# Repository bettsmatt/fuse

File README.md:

# Fuse
A WIP split, 60%, wireless, low profile, choc spaced, magnetic keyboard. 

## Design Notes

* 3D printed case with embedded magnets to allow the two split boards to snap together into a single board. 
* Switches must be soldered as the footprint of hotswap sockets would space the switches too far apart.
* Through hole diode matrix as they look badass and SMD parts are a pain to solder. 
* Wireless (no TRRS), Nice!Nano with 3.7v batteries. Power Switch on PCB.
* PCBs are reversible for the left / right hand. Nice!Nano pins mirrored in ZMK firmware.

## PCB

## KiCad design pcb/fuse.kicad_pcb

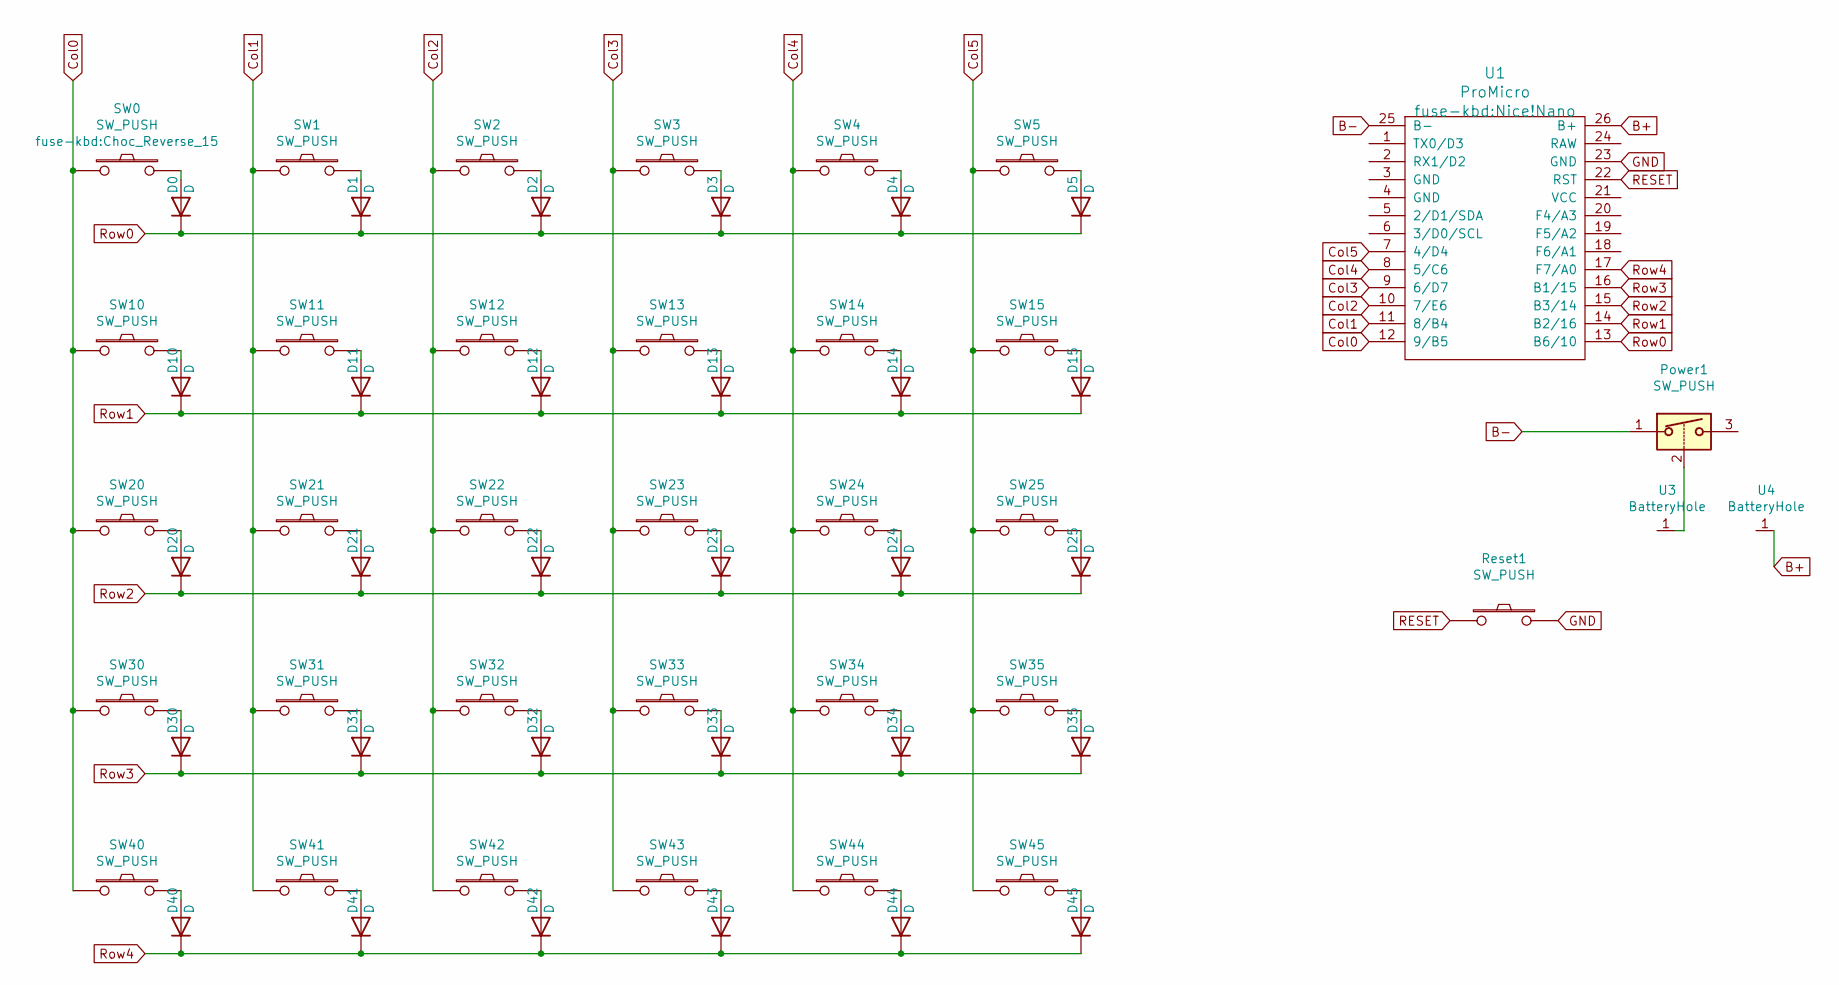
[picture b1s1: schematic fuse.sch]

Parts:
D0, D1, D2, D3, D4, D5, D10, D11, D12, D13, D14, D15, D20, D21, D22, D23, D24, D25, D30, D31, D32, D33, D34, D35, D40, D41, D42, D43, D44, D45: D; R
Power1: SW_PUSH; EG1218
Reset1: SW_PUSH; Reset
SW0, SW10, SW20, SW30, SW45: SW_PUSH; Choc_Reverse_15
SW1, SW2, SW3, SW4, SW5, SW11, SW12, SW13, SW14, SW15, SW21, SW22, SW23, SW24, SW25, SW31, SW32, SW33, SW34, SW35, SW40, SW41, SW42, SW43, SW44: SW_PUSH; Choc_Reverse
U1: ProMicro; Nice!Nano
U3, U4: BatteryHole; BatteryPins

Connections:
B+: U1.26 (B+), U4.1
B-: Power1.1, U1.25 (B-)
Col0: SW0.1, SW10.1, SW20.1, SW30.1, SW40.1, U1.12 (9/B5)
Col1: SW1.1, SW11.1, SW21.1, SW31.1, SW41.1, U1.11 (8/B4)
Col2: SW2.1, SW12.1, SW22.1, SW32.1, SW42.1, U1.10 (7/E6)
Col3: SW3.1, SW13.1, SW23.1, SW33.1, SW43.1, U1.9 (6/D7)
Col4: SW4.1, SW14.1, SW24.1, SW34.1, SW44.1, U1.8 (5/C6)
Col5: SW5.1, SW15.1, SW25.1, SW35.1, SW45.1, U1.7 (4/D4)
GND: Reset1.2, U1.23 (GND)
unnamed: D0.2 (A), SW0.2
unnamed: D1.2 (A), SW1.2
unnamed: D2.2 (A), SW2.2
unnamed: D3.2 (A), SW3.2
unnamed: D4.2 (A), SW4.2
unnamed: D5.2 (A), SW5.2
unnamed: D10.2 (A), SW10.2
unnamed: D11.2 (A), SW11.2
unnamed: D12.2 (A), SW12.2
unnamed: D13.2 (A), SW13.2
unnamed: D14.2 (A), SW14.2
unnamed: D15.2 (A), SW15.2
unnamed: D20.2 (A), SW20.2
unnamed: D21.2 (A), SW21.2
unnamed: D22.2 (A), SW22.2
unnamed: D23.2 (A), SW23.2
unnamed: D24.2 (A), SW24.2
unnamed: D25.2 (A), SW25.2
unnamed: D30.2 (A), SW30.2
unnamed: D31.2 (A), SW31.2
unnamed: D32.2 (A), SW32.2
unnamed: D33.2 (A), SW33.2
unnamed: D34.2 (A), SW34.2
unnamed: D35.2 (A), SW35.2
unnamed: D40.2 (A), SW40.2
unnamed: D41.2 (A), SW41.2
unnamed: D42.2 (A), SW42.2
unnamed: D43.2 (A), SW43.2
unnamed: D44.2 (A), SW44.2
unnamed: D45.2 (A), SW45.2
unnamed: Power1.2, U3.1
RESET: Reset1.1, U1.22 (RST)
Row0: D0.1 (K), D1.1 (K), D2.1 (K), D3.1 (K), D4.1 (K), D5.1 (K), U1.13 (B6/10)
Row1: D10.1 (K), D11.1 (K), D12.1 (K), D13.1 (K), D14.1 (K), D15.1 (K), U1.14 (B2/16)
Row2: D20.1 (K), D21.1 (K), D22.1 (K), D23.1 (K), D24.1 (K), D25.1 (K), U1.15 (B3/14)
Row3: D30.1 (K), D31.1 (K), D32.1 (K), D33.1 (K), D34.1 (K), D35.1 (K), U1.16 (B1/15)
Row4: D40.1 (K), D41.1 (K), D42.1 (K), D43.1 (K), D44.1 (K), D45.1 (K), U1.17 (F7/A0)

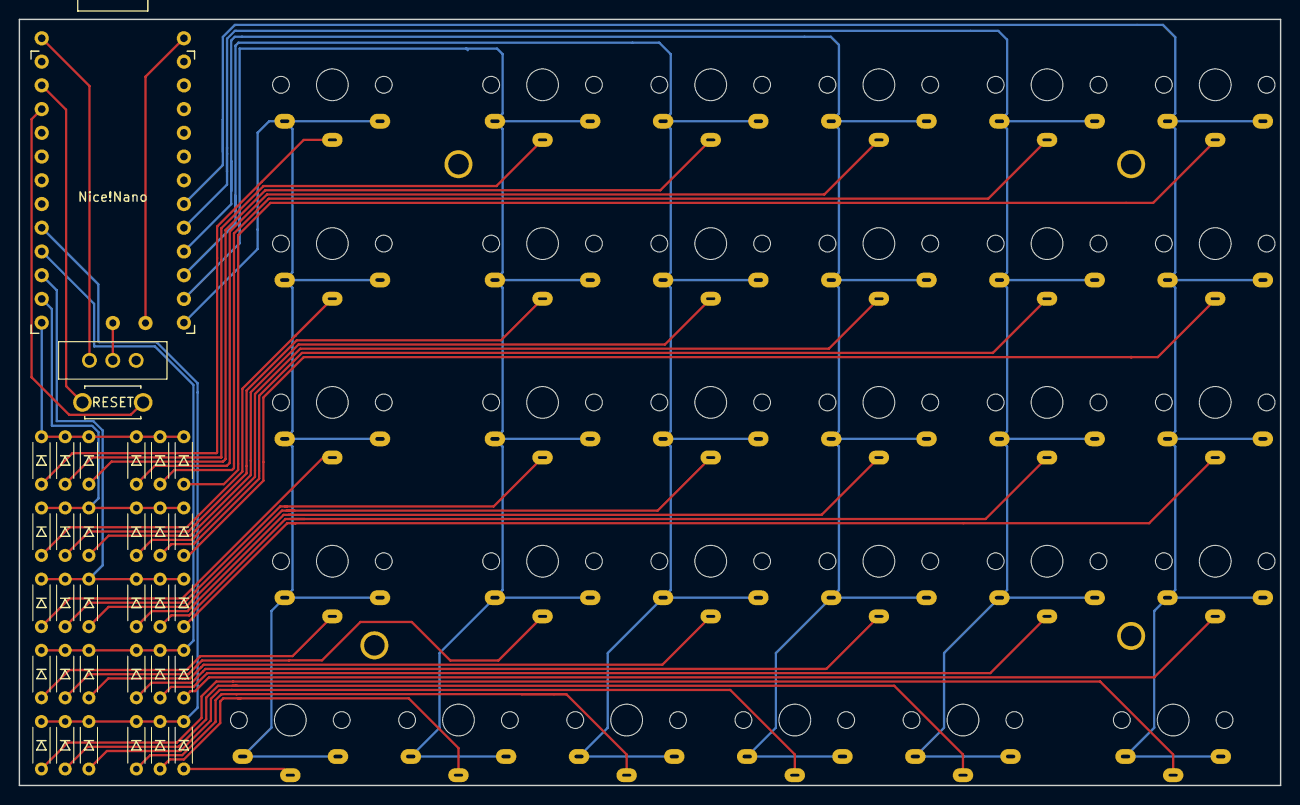
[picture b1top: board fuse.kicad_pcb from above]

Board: 2 copper layers, 135.0 x 82.0 mm, 65 parts (0 on the bottom side), 46 nets.

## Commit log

2022-03-06 Added PCB files.
2022-03-06 Remove hotswap to cut down PCB size.
2022-03-08 fix reset pin and footprints
2022-04-23 Changes for v1 PCB and case
